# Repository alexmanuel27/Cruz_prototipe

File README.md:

# Cruz Prototype

Cruz is an autonomous optical instrument for monitoring natural waters. It is being developed in lakes for eventual use in bays. A single quartz flow cell serves a shared illumination arm with a halogen transmission source and selectable blue, red and infrared LEDs, an inline camera for transmission, and an AS7265x at 90° for fluorescence. The transmission target is 420–780 nm; fluorescence includes nominal 430 nm excitation, with additional red and infrared sources to be tested. A downstream peristaltic pump draws water through the cell. Temperature and conductivity are part of the design.

## Project files

| To work on | Open |
| --- | --- |
| Requirements and design rationale | [Functional specification](ESPECIFICACION.md) · [Decision log](DECISIONES.md) · [Optical design](docs/DISENO_OPTICO.md) |
| Mechanical assembly | [CAD guide](cad/README.md) |
| Fabrication files | [End-cap SVG for Shaper Origin](body/TAPA_SHAPER_230_PROTOTIPO.svg) · [Machining notes](body/LEEME.md) · [R3 attachment ring STL](cad/fusion_m2/ARO_AMARRE_M8_REFORZADO_R3.stl) · [R5 internal chassis STL and assembly guide for Prusa MINI](cad/fusion_m2/chasis_r5/README.md) |
| Electronics | [KiCad V8 project](electronica/cross_v8_raspberry/cross_v8_draft.kicad_pro) · [PCB status and open items](electronica/cross_v8_raspberry/LEEME_PRIMERO.md) |
| Acquisition and control | [Run the monitor](software/README.md) · [Bench tests and V8 interfaces](docs/SOFTWARE_ADQUISICION.md) |
| Test records and simulation data | [Test log](docs/REGISTRO_ENSAYOS.md) · [R3 load and ballast study](cad/fusion_m2/simulacion_amarre_2026-11-20/) · [Calibration procedures](docs/VALIDACION_Y_CALIBRACION.md) |
| Procurement records | [Purchase list](compras/LISTA_COMPRA.md) · [Technician's workbook](compras/Cruz_Shopping_List_EN_2026-10-30.xlsx) |
| Earlier designs and assembly video | [Archive guide](archivo/README.md) |

## Prototype status

The enclosure uses a horizontal clear acrylic tube with a 180 mm outer diameter, a 172 mm inner diameter and a length of 380 mm. Both Ø230 mm end caps use 10 mm acrylic. The auxiliary USB camera looks forward through the front cap. The rear cap service holes will be drilled to suit the actual fittings.

The removable R5 chassis uses two flat-printed end frames and a bolted centre bridge. The optical cradle, cover and PCB tray are removable. All six parts fit the Original Prusa MINI. Fusion v13 documents the R3 attachment ring and ballast simulation. Physical load and leak tests are pending. KiCad V8 is the editable electronics draft. The PCB is currently unrouted: all tracks, copper zones and wire jumpers were removed at Alex’s request. The schematic retains the original connections and numbered functional blocks. Single-sided CNC routing and electrical/mechanical validation remain pending. Purchase prices and quantities in the workbook are dated 30 October 2026.

The [engineering index](docs/INDICE_PROYECTO.md) links to the detailed design, build and validation records.

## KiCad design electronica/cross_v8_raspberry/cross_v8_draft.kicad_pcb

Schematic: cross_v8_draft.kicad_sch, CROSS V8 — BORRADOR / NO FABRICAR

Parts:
C1: 100uF 50V; CNC_Capacitor_THT_CP_Radial_D8_0mm_P3_50mm
C2, C3, C6, C22: 100nF; C_0805_2012Metric
C4, C5: 2u2 X7R 16V; C_0805_2012Metric
C8, C9: 1uF X7R 10V; C_0805_2012Metric
C11, C12: 100nF X7R 25V; C_0805_2012Metric
C15, C20: 22uF X7R 16V; C_1206_3216Metric
C16, C18, C19: 100nF X7R 16V; C_0805_2012Metric
C21: 4u7 X7R 50V; C_1206_3216Metric
D2: 1N4007_PILOT_REVERSE; D_DO-41_SOD81_P10.16mm_Horizontal
D7: PILOT_SIGNAL; D_DO-41_SOD81_P10.16mm_Horizontal
F1: F1_LOAD_RATING_TBD; Fuseholder_Clip-5x20mm_Littelfuse_111_Inline_P20.00x5.00mm_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
J1: RASPBERRY_PI_5_GPIO_3V3; CNC_Connector_IDC_IDC-Header_2x20_P2_54mm_Vertical
J2: MOTOR_COILS_VERIFY; CNC_Connector_PinHeader_2_54mm_PinHeader_1x04_P2_54mm_Verti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
J3: HALOGEN_12V_10W_INRUSH_TBD; TerminalBlock_Phoenix_MKDS-1,5-2-5.08_1x02_P5.08mm_Horizont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
J4: BLUE_LED_420_430nm; TerminalBlock_Phoenix_MKDS-1,5-2-5.08_1x02_P5.08mm_Horizont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
J5: ORANGE_LED_620nm; TerminalBlock_Phoenix_MKDS-1,5-2-5.08_1x02_P5.08mm_Horizont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
J6: ADS1115_INTERFACE_VERIFY; CNC_Connector_PinHeader_2_54mm_PinHeader_1x04_P2_54mm_Verti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
J7: ADS1115_A0_VERIFY; CNC_Connector_PinHeader_2_54mm_PinHeader_1x02_P2_54mm_Verti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
J8: I2C_AS7265X; CNC_Connector_PinHeader_2_54mm_PinHeader_1x04_P2_54mm_Verti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
J10: DS18B20; CNC_Connector_PinHeader_2_54mm_PinHeader_1x03_P2_54mm_Verti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
J11: SYS_SW_DESDE_INTERRUPTOR; TerminalBlock_Phoenix_MKDS-1,5-2-5.08_1x02_P5.08mm_Horizont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
J13: SYS_IN_GESTOR_EXTERNO; TerminalBlock_Phoenix_MKDS-1,5-2-5.08_1x02_P5.08mm_Horizont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
J14: TO_SWITCH_INPUT_FUSED; TerminalBlock_Phoenix_MKDS-1,5-2-5.08_1x02_P5.08mm_Horizont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
J18: EN3_8PIN_ASSIGNMENT_VERIFY; CNC_Connector_PinHeader_2_54mm_PinHeader_1x08_P2_54mm_Verti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
J19: RS485_DFR0845_UART_ADAPTER; CNC_Connector_PinHeader_2_54mm_PinHeader_1x04_P2_54mm_Verti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
J20: RS485_DFR0845_BUS_ADAPTER; CNC_Connector_PinHeader_2_54mm_PinHeader_1x04_P2_54mm_Verti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
J23: PI_5V_USBC_LEAD_VERIFY; TerminalBlock_Phoenix_MKDS-1,5-2-5.08_1x02_P5.08mm_Horizont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
J24: DS3231_5V_GND_SDA_SCL_INT_SQW; CNC_Connector_PinHeader_2_54mm_PinHeader_1x05_P2_54mm_Verti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
J25: PULSADOR_MOMENTANEO_NA_5S; CNC_Connector_PinHeader_2_54mm_PinHeader_1x02_P2_54mm_Verti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
J26: POLOLU_2814_ON_GND; CNC_Connector_PinHeader_2_54mm_PinHeader_1x02_P2_54mm_Verti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
J27: IR_TSHG6410_850nm; TerminalBlock_Phoenix_MKDS-1,5-2-5.08_1x02_P5.08mm_Horizont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
J28: EC_COAX_LIVE_SHIELD_VERIFY; CNC_Connector_PinHeader_2_54mm_PinHeader_1x02_P2_54mm_Verti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
J29: UPDI_5V_SIGNAL_GND; PinHeader_1x03_P2.54mm_Vertical
Q1, Q7, Q8, Q9: IRLZ44N; TO-220-3_Vertical
Q3, Q4: BSS138; SOT-23
R1, R2, R3, R14, R15, R16, R17, R21, R22, R24: 10k; R_0805_2012Metric
R4, R42, R44, R45: 26R 1% 0.25W; CNC_Resistor_THT_R_Axial_DIN0207_L6_3mm_D2_5mm_P7_62mm_Hori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
R5, R36, R38, R40: 470R; R_0805_2012Metric
R6, R37, R39, R41: 120k; R_0805_2012Metric
R8: 100k 1%; R_0805_2012Metric
R9: 10k 1%; R_0805_2012Metric
R10: 4k7; R_0805_2012Metric
R13: 680R; R_0805_2012Metric
R20, R23: 100k; R_0805_2012Metric
R26, R27: 4k7 DNP_VERIFY_MODULE_PULLUPS; R_0805_2012Metric; not fitted
R43, R46: 52R 1% 0.25W; CNC_Resistor_THT_R_Axial_DIN0207_L6_3mm_D2_5mm_P7_62mm_Hori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
R47: 220R 1W CURRENT_TBD; R_Axial_DIN0411_L9.9mm_D3.6mm_P15.24mm_Horizontal
U1: A4988_CARRIER_VERIFY_PINOUT; CNC_Module_Pololu_Breakout-16_15_2x20_3mm
U2: LM317_BLUE_THERMAL_TBD; TO-220-3_Vertical
U3: LTV-817; CNC_Package_DIP_DIP-4_W7_62mm
U4: R-78HE5.0-0.3_AON; CNC_Cross_R78HE5V
U5: EXTERNAL_24V_TO_5V_PI; TerminalBlock_Phoenix_MKDS-1,5-4-5.08_1x04_P5.08mm_Horizont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
U6: EXTERNAL_24V_TO_12V_OPT; TerminalBlock_Phoenix_MKDS-1,5-4-5.08_1x04_P5.08mm_Horizont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
U12: ATLAS_EC_OEM_K0.1_0x64; Atlas_EC_OEM_10pad
U14: LM317_ORANGE_THERMAL_TBD; TO-220-3_Vertical
U16: 74AHCT1G125; SOT-23-5
U17: ATtiny1604-SS; SOIC-14_3.9x8.7mm_P1.27mm

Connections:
3V3_PI: C2.1, C9.1, C18.1, C19.1, J1.1, J6.1, J8.1, J10.1, J19.4, Q3.1 (G), Q4.1 (G), R1.2, R10.2, R14.1, R22.2, R26.1, R27.1, U1.5, U1.6, U1.10, U12.3 (VCC)
5V_AON: C4.1, C5.1, C6.1, C20.1, C22.1, J24.1, J29.1, R13.1, R15.2, R16.2, R17.2, R21.2, R24.2, U4.3 (5V_OUT), U16.5 (VCC), U17.1 (VCC)
5V_PI: C8.1, C15.1, C16.1, J23.1, U5.3
12V_OPT: C11.1, C12.1, J3.1, R47.1, U2.3 (VI), U6.3, U14.3 (VI)
/BAT_SENSE: C3.1, J7.1, R8.2, R9.1
/BLUE_EN: J1.16, R36.1
/BUTTON_N: J25.1, R21.1, U17.11 (PA1)
/CUT_ACK_5V: U16.4, U17.3 (PA5)
/HAL_EN: J1.15, R5.1
/IR_EN: J1.38, R40.1
/M_DIR: J1.12, R3.1, U1.8
/M_ENABLE_N: J1.13, R1.1, U1.1
/M_STEP: J1.11, R2.1, U1.7
/ORANGE_EN: J1.36, R38.1
/PILOT_ACTIVE_N: D7.1 (K), R24.1, U3.4
/PILOT_LED_A: D2.1 (K), R13.2, U3.1
/PILOT_LOOP: D2.2 (A), J18.8, U3.2
/PILOT_SENSE: D7.2 (A), J1.22, R14.2
/POWER_OFF_ACK: J1.37, R23.1, U16.2
/POWER_ON: J26.1, R20.1, U17.13 (PA3)
/RS485_A: J18.5, J20.3
/RS485_B: J18.6, J20.4
/RS485_REF: J18.7, J20.2
/RTC_SCL: J24.4, Q4.3 (D), R16.1
/RTC_SDA: J24.3, Q3.3 (D), R15.1
/SCL: J1.5, J6.4, J8.4, Q4.2 (S), R27.2, U12.8 (SCL)
/SDA: J1.3, J6.3, J8.3, Q3.2 (S), R26.2, U12.1 (SDA)
/SHUTDOWN_REQ_N: J1.29, R22.1, U17.2 (PA4)
/SYS_FUSED: C21.1, F1.2, J14.1, U4.1 (VIN)
/SYS_IN: F1.1, J13.1
/SYS_SW: C1.1, J11.1, R8.1, U1.16, U5.1, U6.1
/TEMP_1WIRE: J1.7, J10.3, R10.1
/UPDI: J29.2, U17.10 (~RESET/PA0)
/WAKE_N: J24.5, R17.1, U17.12 (PA2)
GND: C1.2, C2.2, C3.2, C4.2, C5.2, C6.2, C8.2, C9.2, C11.2, C12.2, C15.2, C16.2, C18.2, C19.2, C20.2, C21.2, C22.2, J1.6, J1.9, J1.14, J1.20, J1.25, J1.30, J1.34, J1.39, J6.2, J7.2, J8.2, J10.2, J11.2, J13.2, J14.2, J18.4, J19.3, J23.2, J24.2, J25.2, J26.2, J29.3, Q1.3 (S), Q7.3 (S), Q8.3 (S), Q9.3 (S), R2.2, R3.2, R6.2, R9.2, R20.2, R23.2, R37.2, R39.2, R41.2, U1.2, U1.3, U1.4, U1.9, U1.15, U3.3, U4.2 (GND), U5.2, U5.4, U6.2, U6.4, U12.6 (GND), U16.1, U16.3 (GND), U17.14 (GND)
unnamed: J1.8, J19.2
unnamed: J1.10, J19.1
unnamed: J2.1, U1.12
unnamed: J2.2, U1.11
unnamed: J2.3, U1.13
unnamed: J2.4, U1.14
unnamed: J3.2, Q1.2 (D)
unnamed: J4.1, R4.2, R42.2, R43.2, U2.1 (ADJ)
unnamed: J4.2, Q7.2 (D)
unnamed: J5.1, R44.2, R45.2, R46.2, U14.1 (ADJ)
unnamed: J5.2, Q8.2 (D)
unnamed: J27.1, R47.2
unnamed: J27.2, Q9.2 (D)
unnamed: J28.1, U12.4 (PRB)
unnamed: J28.2, U12.5 (PRBG)
unnamed: Q1.1 (G), R5.2, R6.1
unnamed: Q7.1 (G), R36.2, R37.1
unnamed: Q8.1 (G), R38.2, R39.1
unnamed: Q9.1 (G), R40.2, R41.1
unnamed: R4.1, R42.1, R43.1, U2.2 (VO)
unnamed: R44.1, R45.1, R46.1, U14.2 (VO)

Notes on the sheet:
NARANJA 620nm
12V_OPT: arranque, fusibles y termica pendientes. Retornos de potencia separados del sensor.
HALOGENA 12V 10W
Pi 5: IDC40 1:1, verificar pin 1. Alimentacion USB-C; J1.2 y J1.4 sin conectar.
J13: salida SYS del gestor externo. Cargador y bateria van al gestor. F1 por dimensionar.
AZUL
08 POTENCIA OPTICA - 12V
IR 850nm
DS3231: conectar INT/SQW a J24.5 (WAKE_N). Verificar orden fisico del modulo.
01 ENTRADA Y PROTECCION
02 CONVERSION DE ALIMENTACION
03 MOTOR PERISTALTICO
04 RASPBERRY Y COMUNICACIONES
05 SENSORES Y CONDUCTIVIDAD
06 RELOJ, ARRANQUE Y APAGADO
07 DETECCION DE PILOTO
DS3231 y adaptacion I2C
Pulsador de 5 s y supervisor permanente
EC-OEM 0x64 y sonda K0.1
PRB/PRBG solo a sonda. Bus I2C de 3V3, 100 kHz.

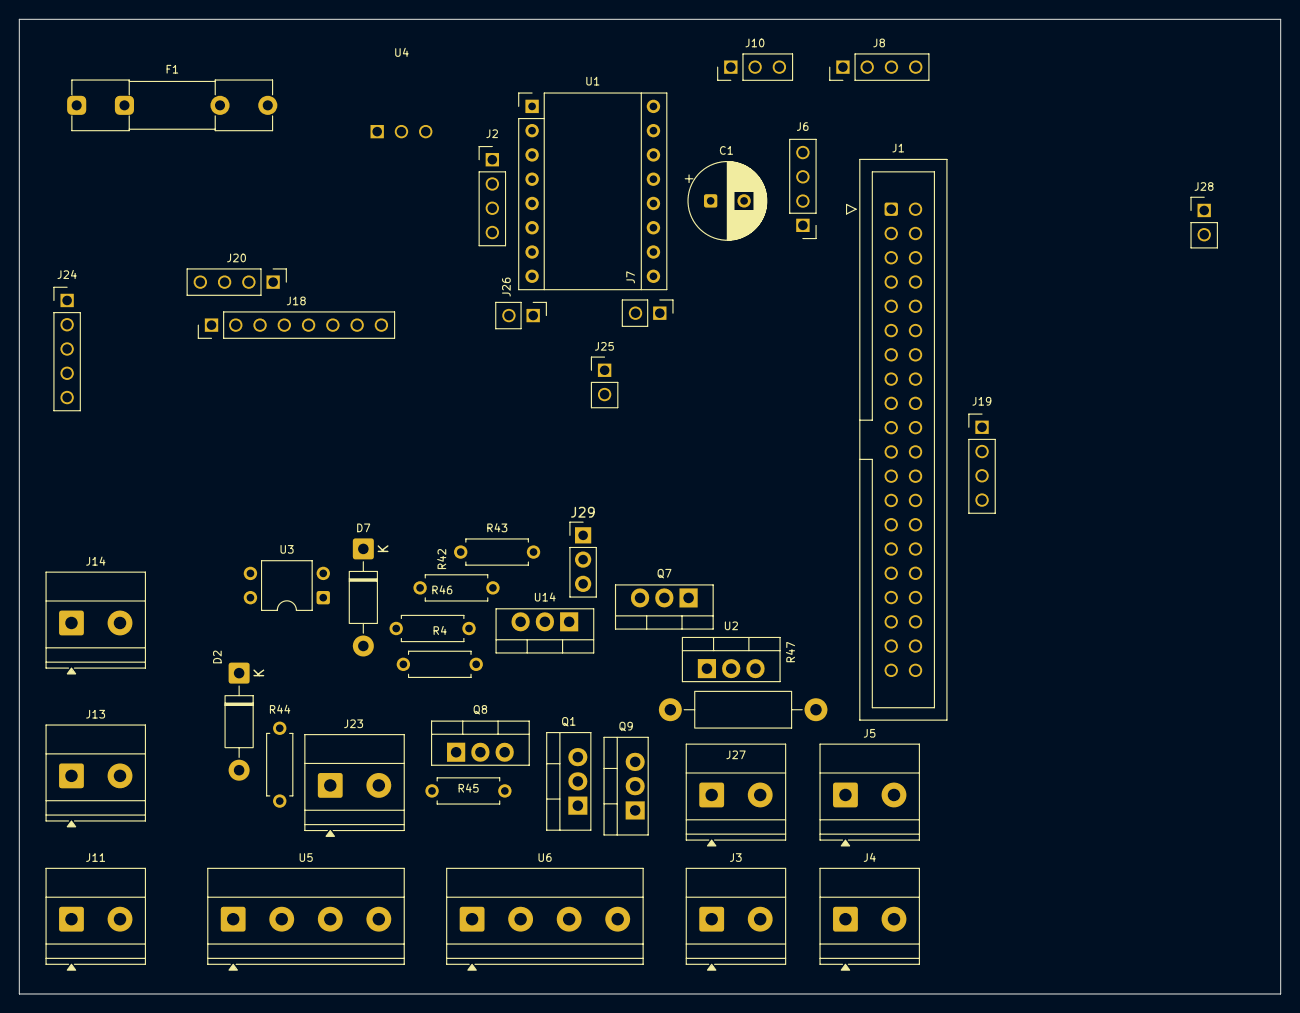
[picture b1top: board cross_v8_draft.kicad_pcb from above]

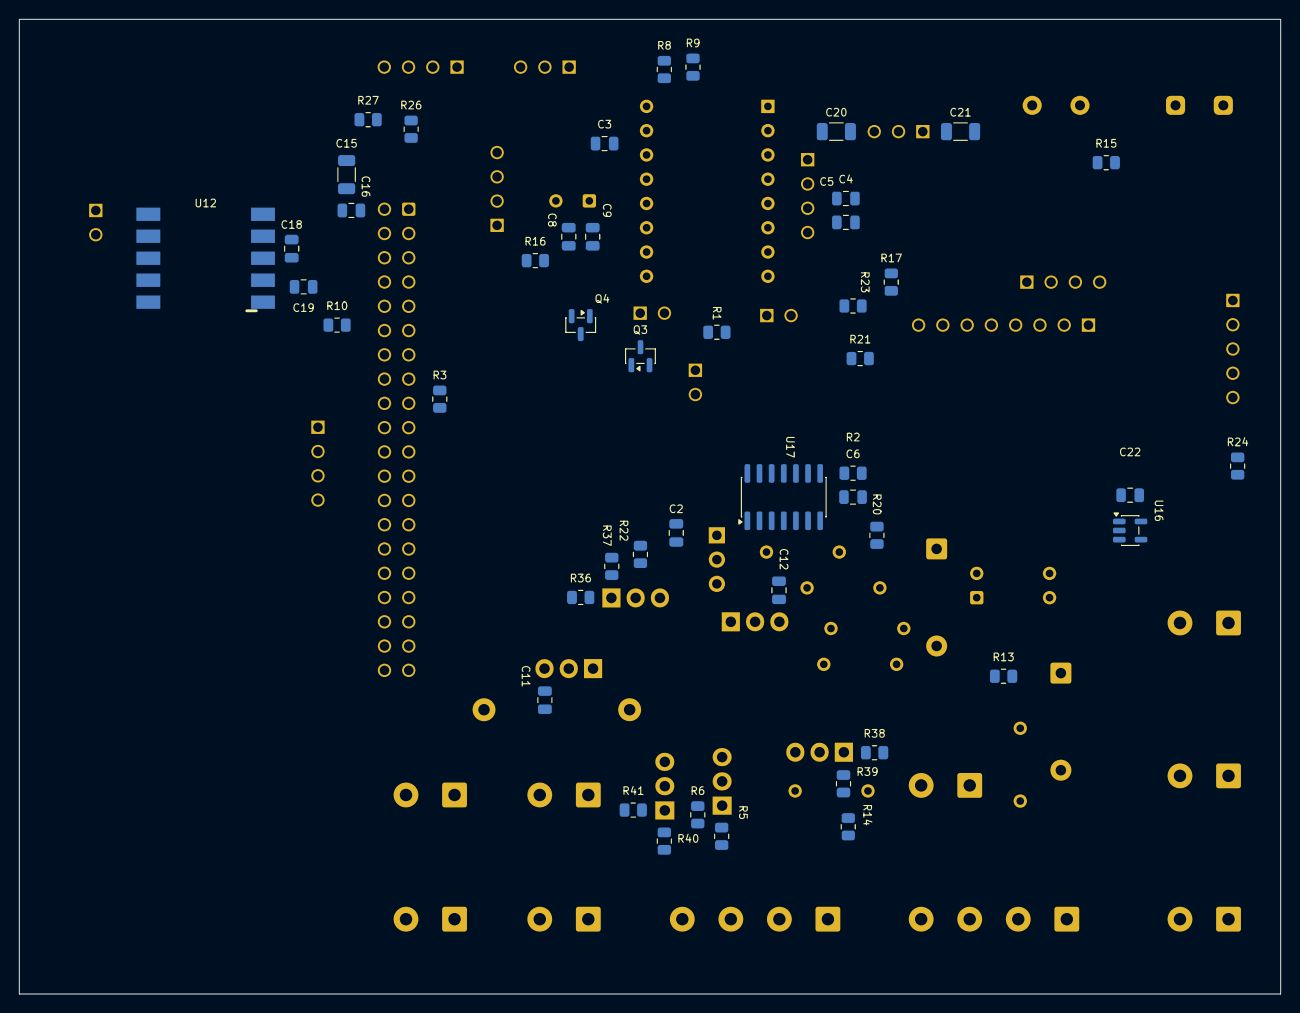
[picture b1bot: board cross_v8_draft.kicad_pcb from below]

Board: 2 copper layers, 132.0 x 102.0 mm, 91 parts (47 on the bottom side), 56 nets, no tracks yet.

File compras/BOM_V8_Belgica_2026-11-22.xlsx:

Cruz V8 · BOM para una PCB
22 nov 2026 · 91 posiciones en KiCad · 89 previstas para montar · 2 DNP · Canti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
Ref. placa | Montar | Componente | Formato | MPN fabricante | Proveedor y código | Pedido | Notas de compra y montaje | Valor en KiCad
C1 | 1 | 100 µF, 50 V, Panasonic FR | Radial Ø8 mm · paso 3,5 mm | EEU-FR1H101 | Mouser BE · 667-EEU-FR1H101 | Pedir | Polarizado. Desacoplo de la alimentación del A4988. | 100uF 50V
C2, C3, C6, C11, C12, C16, C18, C19, C22 | 9 | 100 nF, 50 V, X7R | 0805 | C0805C104K5RACTU | Mouser BE · ficha | Pedir | Una referencia de 50 V cubre los nueve condensadores de 100 nF. | 100nF · 100nF X7R 25V · 100nF X7R 16V
C4, C5 | 2 | 2,2 µF, 25 V, X7R | 0805 | C2012X7R1E225K125AB | Farnell BE · 2526260 | Pedir | El esquema especifica 16 V como mínimo. | 2u2 X7R 16V
C8, C9 | 2 | 1 µF, 25 V, X7R | 0805 | C0805C105K3RACTU | Mouser BE · ficha | Pedir | El esquema especifica 10 V como mínimo. | 1uF X7R 10V
C15, C20 | 2 | 22 µF, 16 V, X7R | 1206 | 1206YC226MAT2A | Mouser BE · 581-1206YC226MAT2A | Pedir | Carriles de 5 V. Confirmar disponibilidad en el formato de cinta cortada. | 22uF X7R 16V
C21 | 1 | 4,7 µF, 50 V, X7R | 1206 | C1206X475K5RACAUTO | Mouser BE · ficha | Pedir | En la entrada SYS_FUSED. | 4u7 X7R 50V
D2 | 1 | Diodo rectificador del piloto | DO-41 axial · paso 10,16 mm | 1N4007-E3/73 | Farnell BE · 2395843 | Pedir | Protección inversa del piloto. | 1N4007_PILOT_REVERSE
D7 | 1 | Diodo de señal del piloto | DO-41 axial · paso 10,16 mm | 1N5819-E3/54 | Farnell BE · 1336533 | Validar | Candidato Schottky de baja caída. Medir nivel bajo en GPIO 22 con el piloto act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 | PILOT_SIGNAL
F1 | 1 | Posición de fusible de carga | Clips 5×20 mm en PCB | Calibre pendiente |  | Validar | Medir corriente y pico de arranque. Alternativa de portafusible externo en la s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 | F1_LOAD_RATING_TBD
J1 | 1 | Cabezal macho IDC, 2×20 con guía | THT vertical · paso 2,54 mm | N2540-6002RB | Farnell BE · 9838309 | Pedir | Usar la cinta 1:1. Comprobar pin 1 en ambos extremos. | RASPBERRY_PI_5_GPIO_3V3
J2, J6, J8, J19, J20 | 5 | Cabezal macho 1×4 | THT vertical · paso 2,54 mm | TSW-104-07-G-S | Mouser BE · ficha | Pedir | Motor, ADS1115, AS7265x y ambos lados del adaptador RS485. | MOTOR_COILS_VERIFY · ADS1115_INTERFACE_VERIFY · I2C_AS7265X · RS485_DFR0845_UAR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
J7, J25, J26, J28 | 4 | Cabezal macho 1×2 | THT vertical · paso 2,54 mm | TSW-102-07-G-S | Mouser BE · ficha | Pedir | Entrada analógica, pulsador, mando Pololu y sonda EC. | ADS1115_A0_VERIFY · PULSADOR_MOMENTANEO_NA_5S · POLOLU_2814_ON_GND · EC_COAX_LI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
J10, J29 | 2 | Cabezal macho 1×3 | THT vertical · paso 2,54 mm | TSW-103-07-G-S | Mouser BE · ficha | Pedir | DS18B20 y programación UPDI. | DS18B20 · UPDI_5V_SIGNAL_GND
J24 | 1 | Cabezal macho 1×5 | THT vertical · paso 2,54 mm | TSW-105-07-G-S | Mouser BE · ficha | Pedir | DS3231 con INT/SQW. Cotejar el orden de los hilos. | DS3231_5V_GND_SDA_SCL_INT_SQW
J18 | 1 | Cabezal macho 1×8 | THT vertical · paso 2,54 mm | TSW-108-07-G-S | Mouser BE · ficha | Pedir | Conexión interna al EN3 de panel. | EN3_8PIN_ASSIGNMENT_VERIFY
J3, J4, J5, J11, J13, J14, J23, J27 | 8 | Bornera Phoenix Contact MKDS 1,5/2-5,08 | 2 polos · paso 5,08 mm | 1715721 | RS BE · 1930564 | Pedir | Entrada, rama conmutada, alimentación Pi y cuatro fuentes ópticas. | HALOGEN_12V_10W_INRUSH_TBD · BLUE_LED_420_430nm · ORANGE_LED_620nm · SYS_SW_DES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
U5, U6 | 2 | Bornera Phoenix Contact MKDS 1,5/4-5,08 | 4 polos · paso 5,08 mm | 1715747 | RS BE · 6487857 | Pedir | Son las dos borneras de entrada/salida de los DC/DC externos. | EXTERNAL_24V_TO_5V_PI · EXTERNAL_24V_TO_12V_OPT
Q1, Q7, Q8, Q9 | 4 | MOSFET Infineon IRLZ44N | TO-220AB vertical | IRLZ44NPBF | Farnell BE · 8651418 | Revisar inventario | Has probado esta familia con 3,3 V. Medir calentamiento y arranque en frío de l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 | IRLZ44N
Q3, Q4 | 2 | MOSFET BSS138 onsemi | SOT-23 | BSS138LT1G | Mouser BE · 863-BSS138LT1G | Pedir | Adaptación de niveles del I²C del RTC. | BSS138
R1, R2, R3, R9, R14, R15, R16, R17, R21, R22, R24 | 11 | 10 kΩ, 1 %, 0,125 W | 0805 | RC0805FR-0710KL | Mouser BE · 603-RC0805FR-0710KL | Pedir |  | 10k · 10k 1%
R5, R36, R38, R40 | 4 | 470 Ω, 1 %, 0,125 W | 0805 | RC0805FR-07470RL | Mouser BE · ficha | Pedir | Resistencias de puerta de los cuatro IRLZ44N. | 470R
R6, R37, R39, R41 | 4 | 120 kΩ, 1 %, 0,125 W | 0805 | RC0805FR-07120KL | Mouser BE · ficha | Pedir |  | 120k
R8, R20, R23 | 3 | 100 kΩ, 1 %, 0,125 W | 0805 | RC0805FR-07100KL | Mouser BE · ficha | Pedir | R8 forma el divisor de telemetría con R9. | 100k 1% · 100k
R10 | 1 | 4,7 kΩ, 1 %, 0,125 W | 0805 | RC0805FR-074K7L | Mouser BE · ficha | Pedir | Pull-up del DS18B20. | 4k7
R13 | 1 | 680 Ω, 1 %, 0,125 W | 0805 | RC0805FR-07680RL | Mouser BE · ficha | Pedir |  | 680R
R4, R42, R44, R45 | 4 | 26 Ω en KiCad · 26,1 Ω propuesto | DIN0207 axial · paso 7,62 mm | MFR-25FBF52-26R1 | Mouser BE · ficha | Validar | 1 %, 0,25 W. Si tienes las de 26 Ω que probaste, úsalas. Validar corriente con 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 | 26R 1% 0.25W
R43, R46 | 2 | 52 Ω en KiCad · 52,3 Ω propuesto | DIN0207 axial · paso 7,62 mm | MFR-25FBF52-52R3 | Mouser BE · ficha | Validar | 1 %, 0,25 W. Con 26,1 Ω ∥ 26,1 Ω ∥ 52,3 Ω, consigna ideal ≈119,7 mA. | 52R 1% 0.25W
R47 | 1 | 220 Ω, 5 %, 1 W | Axial · paso de placa 15,24 mm | PR01000102200JA100 | Farnell BE · 2614507 | Pedir | Cuerpo menor que DIN0411. Formar patas al paso de la placa. Verificar corriente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 | 220R 1W CURRENT_TBD
U1 | 1 | Portador A4988 para el motor | Módulo 2×8 · paso 2,54 mm | A4988 existente | Ficha del fabricante | Ya tienes | Ficha del Pololu como referencia. Cotejar pinout, resistencia de sense y límite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 | A4988_CARRIER_VERIFY_PINOUT
U2, U14 | 2 | Regulador ajustable LM317T ST | TO-220 vertical | LM317T | Farnell BE · 9756027 | Pedir 1 si el tuyo encaja | Se montan dos. Tienes uno. Verificar potencia disipada con los LED reales. | LM317_BLUE_THERMAL_TBD · LM317_ORANGE_THERMAL_TBD
U3 | 1 | Optoacoplador Lite-On LTV-817 | DIP-4 · ancho de filas 7,62 mm | LTV-817 | Mouser BE · ficha | Pedir | Lectura del piloto. | LTV-817
U4 | 1 | RECOM 5 V / 300 mA de espera | SIP-3 | R-78HE5.0-0.3 | Farnell BE · 3264795 | Pedir | Alimenta supervisor y RTC. Entrada 6,5–72 V según RECOM. | R-78HE5.0-0.3_AON
U12 | 1 | Módulo de conductividad Atlas EC-OEM | Módulo de 10 contactos | EC-OEM existente | Ficha del fabricante | Ya tienes | Recibe 3V3 de la Pi y comparte I²C. Verificar encaje y orientación antes de sol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 | ATLAS_EC_OEM_K0.1_0x64
U16 | 1 | Buffer lógico TI de confirmación de apagado | SOT-23-5 (DBV) | SN74AHCT1G125DBVR | Mouser BE · 595-SNAHCT1G125DBVR | Pedir | Función de apagado. Adaptación de 3,3 a 5 V. | 74AHCT1G125
U17 | 1 | Microcontrolador Microchip ATtiny1604 | SOIC-14 · paso 1,27 mm | ATTINY1604-SSNR | Mouser BE · ficha | Pedir | Programar por J29 con el firmware de pulsación de 5 s. | ATtiny1604-SS
R26, R27 | 0 | 4,7 kΩ, pull-ups opcionales | 0805 | RC0805FR-074K7L |  | DNP · sin montar | Colocar solo si la revisión del bus I²C lo requiere. Misma referencia que R10. | 4k7 DNP_VERIFY_MODULE_PULLUPS

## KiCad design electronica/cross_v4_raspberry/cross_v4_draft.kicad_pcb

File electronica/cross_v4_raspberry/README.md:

# PCB V4 — carga con batería de terminales comunes

**Estado: borrador incompleto. No fabricar, soldar ni energizar.** V4 conserva el trabajo V3 en una carpeta aparte e incorpora el ramal de carga solicitado el 2 de noviembre de 2026.

## Cambios incorporados en KiCad

- `J13`: entrada del par común del pack. La alimentación y la carga comparten el mismo positivo (`VBAT_RAW`) y el mismo negativo (`GND`).
- `F1`: fusible provisional del ramal de consumo. `J14` lleva su salida a un interruptor de potencia que aún debe diseñarse; `J11` recibe por separado la salida conmutada. **J14 y J11 no están conectados entre sí en esta placa**.
- `F2`: fusible provisional de carga, en la rama positiva entre batería y el contacto común de `K1`.
- `K1`: relé bipolar G2RL-2 de bobina 5 V; los contactos normalmente abiertos conectan `J15` a los dos bornes del pack cuando se excita. `Q2`, resistencias y diodo de rueda libre representan el control de la bobina.
- `J16`, `U3`, resistencias y diodo: circuito provisional de detección del bucle de presencia del cable. `J16` representa las dos señales de presencia, no la asignación física definitiva del conector exterior. La Raspberry lee el estado mediante GPIO25; GPIO24 controla el relé mediante Q2.
- `J17` es únicamente una entrada provisional de `5V_AON` para el relé y el piloto: **su fuente no está diseñada en esta versión**. El encendido de la Raspberry para modo servicio no está resuelto.

La apertura de K1 con la pérdida del cable depende de software y de que la Raspberry esté operativa: **no hay un enclavamiento cableado independiente ni garantía de liberación ante cuelgue**. No hay firmware de control, detector de fugas integrado, prueba de interbloqueo ni solución para cargar con batería agotada. El pinout de ocho contactos del puerto exterior, polaridad del pack, corriente del cargador, BMS, características definitivas de fusibles, conexión a la futura boya y verificación de interruptores/pistas siguen pendientes. El circuito propuesto no sustituye el cargador original ni puentea el BMS.

Las huellas de conectores/fusibles son provisionales. Se eligieron clips 5 × 20 mm y relé G2RL-2 DC5 para poder estudiar el montaje; no se ha aprobado su compra ni determinado si son adecuados para corriente, capacidad de corte DC y condiciones térmicas reales. Los pines de J15/J16 **no son el pinout del conector exterior EN3**. La placa Atlas J9 conserva una propuesta de cinco pines y necesita comprobación de revisión, orientación y soporte.

## Comprobaciones de KiCad

- Se compararon las redes exportadas por el esquema con las conexiones previstas de la placa. Durante la generación se detectó y corrigió una unión indebida de 5 V con masa, y se restauró el pin de bobina `K1.A2`. Esta comparación no valida el circuito ni la seguridad de los componentes.
- DRC con paridad: **106 conexiones sin trazar**, **25 avisos de serigrafía** y **0 diferencias de paridad**. La placa no es fabricable.
- ERC: **126 incidencias**: 2 errores de alimentación no declarada, 81 avisos de puntos fuera de la rejilla y 43 avisos de discrepancia de símbolos. Se requiere revisar y ordenar el esquema, resolver ERC y comprobar visualmente cada conexión.
- No se han calculado pistas ni verificado rutas de corriente, ventilación o temperatura. No hay pruebas físicas.

## Fusion

El STEP de referencia es [`PCB_V4_BORRADOR_NO_FABRICAR.step`](../../cad/fusion_m2/PCB_V4_BORRADOR_NO_FABRICAR.step). Se importó como `PCB_V4_CARGA_BORRADOR_NO_FABRICAR` al documento activo `Cross_M2_horizontal_design`; se ocultó la referencia V3 sin borrarla. **El documento de Fusion quedó sin guardar.** La colocación es provisional, sin taladros de fijación ni cálculo de interferencias. Actualización 3D: se incorporaron modelos de referencia del relé y A4988, zócalos y envolventes aproximadas de disipador y fusibles. Procedencia, hipótesis y componentes aún pendientes en [modelos 3D](modelos_3d/README.md). Los componentes y conectores no están aprobados. Los DC/DC y otros módulos de potencia tampoco se han integrado.

Fuentes: [ficha Omron G2RL](https://omronfs.omron.com/en_US/ecb/products/pdf/en-g2rl.pdf), [AO3400A](https://www.aosmd.com/products/mosfets/low-voltage-mosfets-12v-30v/ao3400a), [DFR1015](https://www.dfrobot.com/product-2599.html), [Atlas carrier Gen 2](https://files.atlas-scientific.com/electrically-isolated-ezo-carrier-board.pdf).

**Actualización de Fusion:** el STEP más reciente es `PCB_V4_REFERENCIAS_3D_BORRADOR.step`; la versión anterior quedó oculta sin borrar. Se mantienen las limitaciones y solapamientos de referencias previos. La placa sigue sin rutear ni validar.

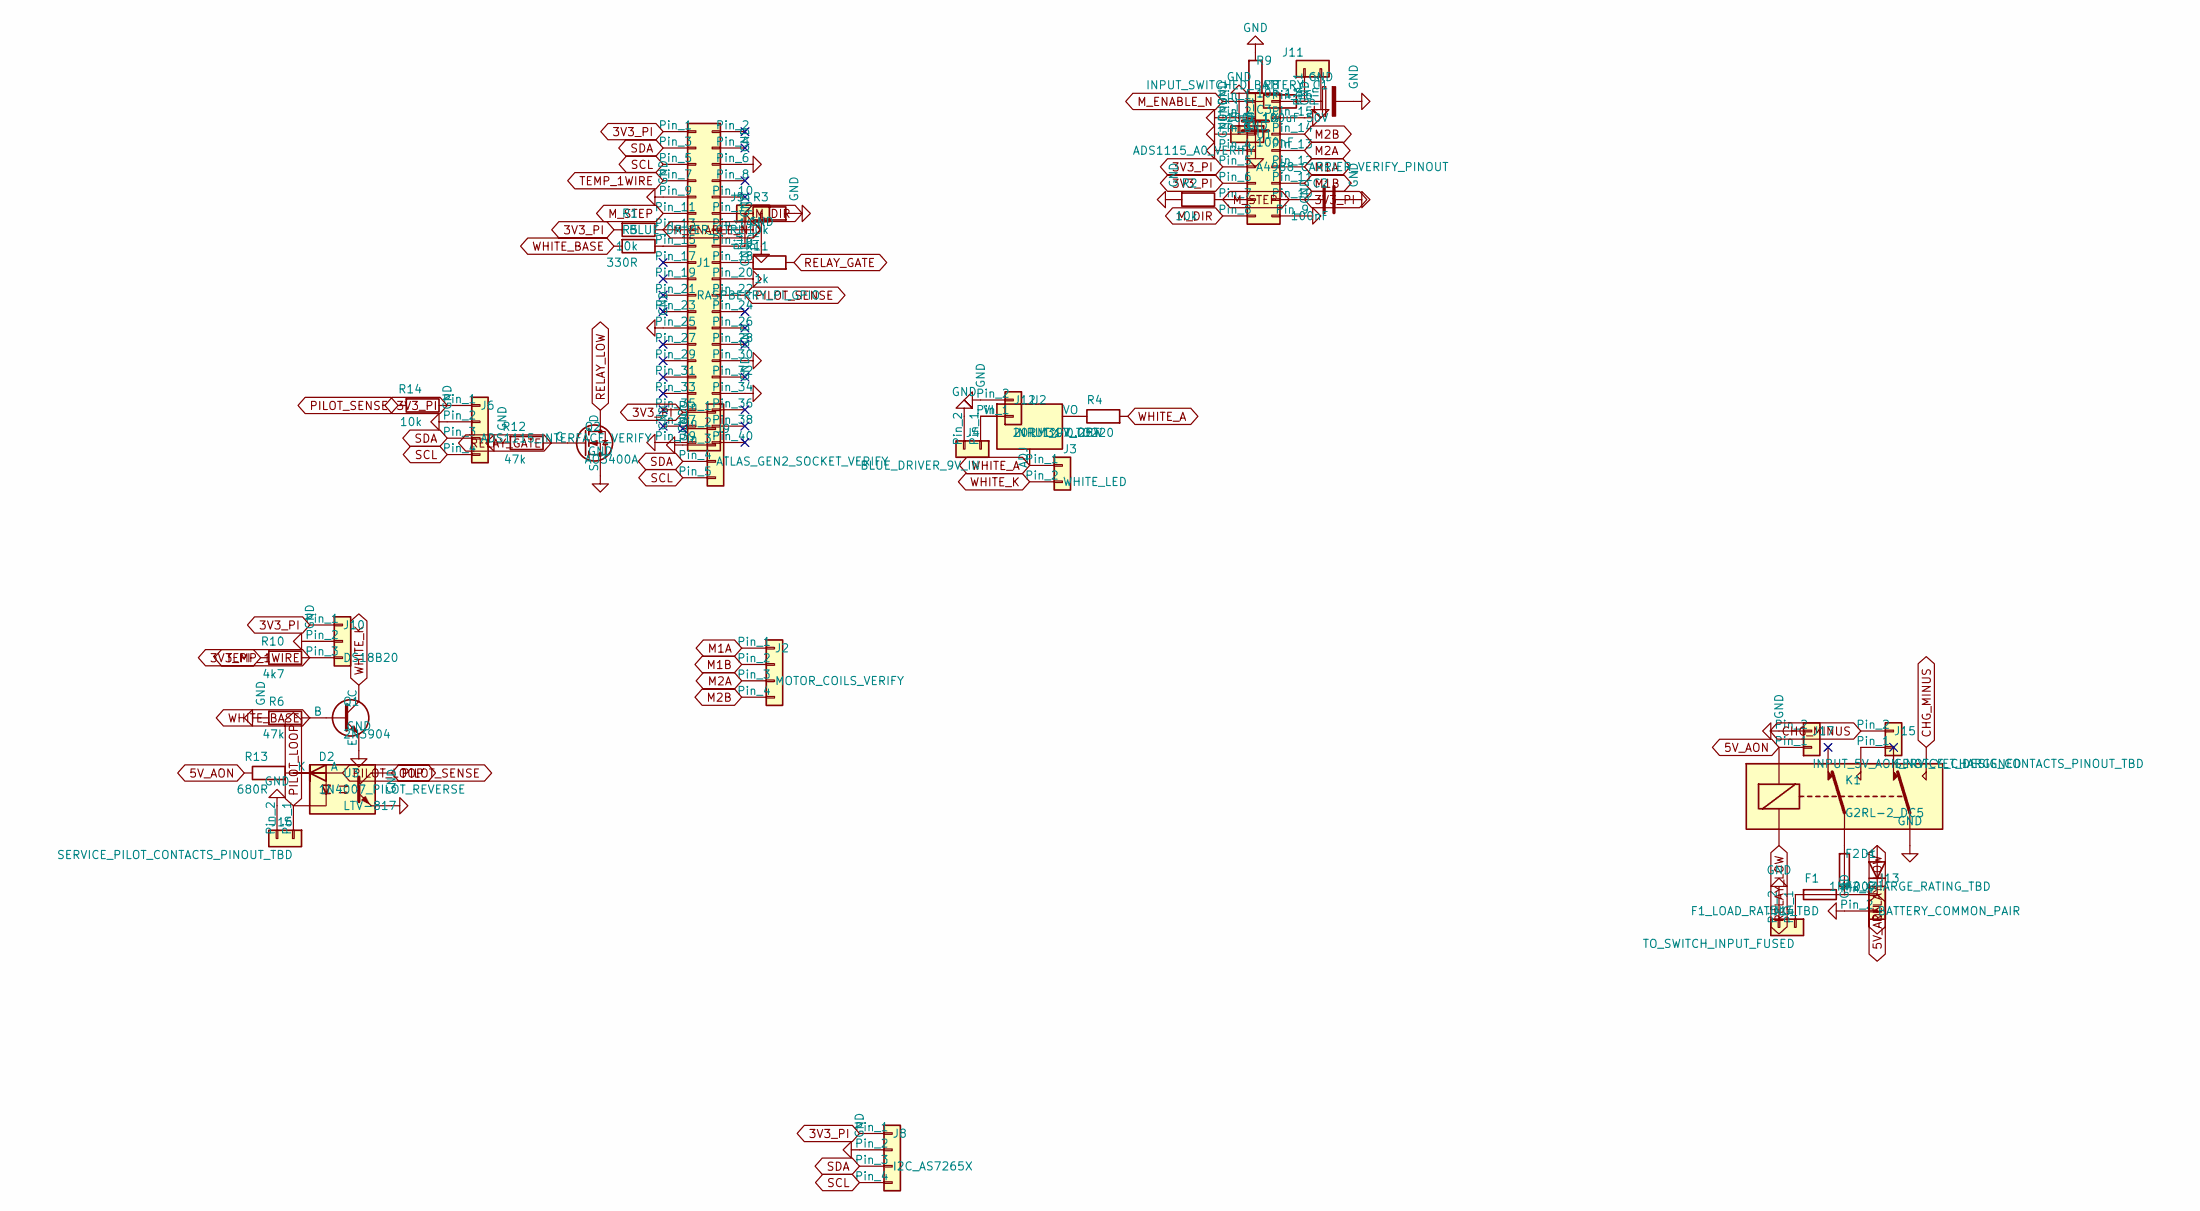
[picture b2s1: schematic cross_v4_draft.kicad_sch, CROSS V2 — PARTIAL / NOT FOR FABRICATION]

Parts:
C1: 100uF 50V; CP_Radial_D8.0mm_P3.50mm
C2, C3: 100nF; C_Disc_D5.0mm_W2.5mm_P5.00mm
D1: 1N4007; D_DO-41_SOD81_P10.16mm_Horizontal
D2: 1N4007_PILOT_REVERSE; D_DO-41_SOD81_P10.16mm_Horizontal
F1: F1_LOAD_RATING_TBD; Fuseholder_Clip-5x20mm_Littelfuse_111_Inline_P20.00x5.00mm_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
F2: F2_CHARGE_RATING_TBD; Fuseholder_Clip-5x20mm_Littelfuse_111_Inline_P20.00x5.00mm_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
J1: RASPBERRY_PI_GPIO; PinHeader_2x20_P2.54mm_Vertical
J2: MOTOR_COILS_VERIFY; PinHeader_1x04_P2.54mm_Vertical
J3: WHITE_LED; PinHeader_1x02_P2.54mm_Vertical
J4: BLUE_DRIVER_9V_IN; PinHeader_1x02_P2.54mm_Vertical
J5: BLUE_DRIVER_CTRL; PinHeader_1x02_P2.54mm_Vertical
J6: ADS1115_INTERFACE_VERIFY; PinHeader_1x04_P2.54mm_Vertical
J7: ADS1115_A0_VERIFY; PinHeader_1x02_P2.54mm_Vertical
J8: I2C_AS7265X; PinHeader_1x04_P2.54mm_Vertical
J9: ATLAS_GEN2_SOCKET_VERIFY; PinSocket_1x05_P2.54mm_Vertical
J10: DS18B20; PinHeader_1x03_P2.54mm_Vertical
J11: INPUT_SWITCHED_BATTERY; PinHeader_1x02_P2.54mm_Vertical
J12: INPUT_9V_OPT; PinHeader_1x02_P2.54mm_Vertical
J13: BATTERY_COMMON_PAIR; PinHeader_1x02_P2.54mm_Vertical
J14: TO_SWITCH_INPUT_FUSED; PinHeader_1x02_P2.54mm_Vertical
J15: SERVICE_CHARGE_CONTACTS_PINOUT_TBD; PinHeader_1x02_P2.54mm_Vertical
J16: SERVICE_PILOT_CONTACTS_PINOUT_TBD; PinHeader_1x02_P2.54mm_Vertical
J17: INPUT_5V_AON_NOT_YET_DESIGNED; PinHeader_1x02_P2.54mm_Vertical
K1: G2RL-2_DC5; Relay_DPDT_Omron_G2RL-2
Q1: 2N3904; TO-92_Inline
Q2: AO3400A; SOT-23
R1, R2, R3, R14: 10k; R_Axial_DIN0207_L6.3mm_D2.5mm_P7.62mm_Horizontal
R4: 20R 1% 0.25W; R_Axial_DIN0207_L6.3mm_D2.5mm_P7.62mm_Horizontal
R5: 330R; R_Axial_DIN0207_L6.3mm_D2.5mm_P7.62mm_Horizontal
R6, R12: 47k; R_Axial_DIN0207_L6.3mm_D2.5mm_P7.62mm_Horizontal
R8: 100k 1%; R_Axial_DIN0207_L6.3mm_D2.5mm_P7.62mm_Horizontal
R9: 10k 1%; R_Axial_DIN0207_L6.3mm_D2.5mm_P7.62mm_Horizontal
R10: 4k7; R_Axial_DIN0207_L6.3mm_D2.5mm_P7.62mm_Horizontal
R11: 1k; R_Axial_DIN0207_L6.3mm_D2.5mm_P7.62mm_Horizontal
R13: 680R; R_Axial_DIN0207_L6.3mm_D2.5mm_P7.62mm_Horizontal
U1: A4988_CARRIER_VERIFY_PINOUT; Pololu_Breakout-16_15.2x20.3mm
U2: LM317_TO220; TO-220-3_Vertical
U3: LTV-817; DIP-4_W7.62mm

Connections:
3V3_PI: C2.1, J1.1, J6.1, J8.1, J9.1, J10.1, R1.2, R10.2, R14.1, U1.5, U1.6, U1.10
5V_AON: D1.1 (K), J17.1, K1.A1, R13.1
CHG_MINUS: J15.2, K1.24
GND: C1.2, C2.2, C3.2, J1.6, J1.9, J1.14, J1.20, J1.25, J1.30, J1.34, J1.39, J4.2, J5.2, J6.2, J7.2, J8.2, J9.3, J10.2, J11.2, J12.2, J13.2, J14.2, J16.2, J17.2, K1.21, Q1.1 (E), Q2.2 (S), R2.2, R3.2, R6.2, R9.2, R12.2, U1.2, U1.3, U1.4, U1.9, U1.15, U3.3
M1A: J2.1, U1.12
M1B: J2.2, U1.11
M2A: J2.3, U1.13
M2B: J2.4, U1.14
M_DIR: J1.12, R3.1, U1.8
M_ENABLE_N: J1.13, R1.1, U1.1
M_STEP: J1.11, R2.1, U1.7
unnamed: D2.1 (K), R13.2, U3.1
unnamed: F2.2, K1.11
unnamed: J1.15, R5.1
unnamed: J1.16, J5.1
unnamed: J1.18, R11.1
unnamed: C3.1, J7.1, R8.2, R9.1
unnamed: C1.1, J11.1, R8.1, U1.16
unnamed: J4.1, J12.1, U2.3 (VI)
unnamed: F1.1, F2.1, J13.1
unnamed: F1.2, J14.1
unnamed: J15.1, K1.14
unnamed: R4.1, U2.2 (VO)
PILOT_LOOP: D2.2 (A), J16.1, U3.2
PILOT_SENSE: J1.22, R14.2, U3.4
RELAY_GATE: Q2.1 (G), R11.2, R12.1
RELAY_LOW: D1.2 (A), K1.A2, Q2.3 (D)
SCL: J1.5, J6.4, J8.4, J9.5
SDA: J1.3, J6.3, J8.3, J9.4
TEMP_1WIRE: J1.7, J10.3, R10.1
WHITE_A: J3.1, R4.2, U2.1 (ADJ)
WHITE_BASE: Q1.2 (B), R5.2, R6.1
WHITE_K: J3.2, Q1.3 (C)

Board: 2 copper layers, 43 parts (0 on the bottom side), 33 nets, no tracks yet.

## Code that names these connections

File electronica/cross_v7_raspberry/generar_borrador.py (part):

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for pin in [2,4,17,19,21,23,24,26,27,28,31,32,33,35,36,38,40]: p[pin] += NC
# Driver carrier has Pololu-compatible pin order: confirm physical red carrier before insertion.
m=part('Connector_Generic','Conn_02x08_Counter_Clockwise','U1','A4988_CARRIER_VERIFY_PINOUT','Module:Pololu_Breakout-16_15.2x20.3mm')
for pin,n in {1:'M_ENABLE_N',2:'GND',3:'GND',4:'GND',5:'3V3_PI',6:'3V3_PI',7:'M_STEP',8:'M_DIR',9:'GND',10:'3V3_PI',11:'M1B',12:'M1A',13:'M2A',14:'M2B',15:'GND',16:'VBAT_SW'}.items(): net(n,m[pin])
r('R1','10k','M_ENABLE_N','3V3_PI');r('R2','10k','M_STEP','GND');r('R3','10k','M_DIR','GND')
c=part('Device','C_Polarized','C1','100uF 50V','Capacitor_THT:CP_Radial_D8.0mm_P3.50mm');net('VBAT_SW',c[1]);net('GND',c[2])
c=part('Device','C','C2','100nF',cap);net('3V3_PI',c[1]);net('GND',c[2])
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# Common battery pair and dual isolated charging contacts; fuse ratings to be selected.
connector('J13','BATTERY_COMMON_PAIR',2,['VBAT_RAW','GND'])
connector('J14','TO_SWITCH_INPUT_FUSED',2,['VBAT_FUSED','GND'])
connector('J18','EN3_8PIN_ASSIGNMENT_VERIFY',8,['CHG_PLUS','CHG_MINUS',None,'GND','RS485_A','RS485_B','RS485_REF','PILOT_LOOP'])
connector('J19','RS485_DFR0845_UART_ADAPTER',4,['UART_RX','UART_TX','GND','3V3_PI'])
connector('J20','RS485_DFR0845_BUS_ADAPTER',4,[None,'RS485_REF','RS485_A','RS485_B'])
connector('J23','PI_5V_USBC_LEAD_VERIFY',2,['5V_PI','GND'])
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f=part('Device','Fuse','F1','F1_LOAD_RATING_TBD',fusefp);net('VBAT_RAW',f[1]);net('VBAT_FUSED',f[2])
f=part('Device','Fuse','F2','F2_CHARGE_RATING_TBD',fusefp);net('VBAT_RAW',f[1]);net('CHG_FUSED',f[2])
k=part('Relay','G2RL-2','K1','G2RL-2_DC5','Relay_THT:Relay_DPDT_Omron_G2RL-2')
for pin,n in {'A1':'5V_AON','A2':'RELAY_LOW','11':'CHG_FUSED','14':'CHG_PLUS','21':'GND','24':'CHG_MINUS'}.items():net(n,k[pin])
k['12'] += NC
k['22'] += NC
q2=part('Transistor_FET','AO3400A','Q2','AO3400A','Package_TO_SOT_SMD:SOT-23')
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net('Q5_BASE',p['B']);net('GND',p['E']);net('SET_NODE',p['C'])
r('R20','100k','POWER_ON','GND');r('R23','100k','HOLD_PI','GND')
u=part('4xxx','4013','U8','CD4013_LATCH_PROVISIONAL','Package_DIP:DIP-14_W7.62mm')
for pin,n in {5:'GND',3:'GND',6:'SET_NODE',4:'HOLD_PI',1:'POWER_ON',9:'GND',11:'GND',8:'GND',10:'GND',14:'3V3_AON',7:'GND'}.items():net(n,u[pin])
for pin in [2,12,13]:u[pin] += NC
p=part('Device','C','C6','100nF',cap);net('3V3_AON',p[1]);net('GND',p[2])
# Hardware charge interlock; independent of Pi command when pilot loop is open.
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# Blue driver is disabled during Pi boot by a pull-up and shunt FET; active-low GPIO.
r('R25','4k7','BLUE_GATE','3V3_PI')
p=part('Transistor_FET','AO3400A','Q7','BLUE_DISABLE_FET','Package_TO_SOT_SMD:SOT-23');net('BLUE_GATE',p['G']);net('BLUE_CTRL',p['D']);net('GND',p['S'])
d=part('Diode','1N5819','D8','BLUE_GPIO_INVERT','Diode_THT:D_DO-41_SOD81_P10.16mm_Horizontal');net('BLUE_GATE',d['A']);net('BLUE_EN',d['K'])
# Magnet N/O reed is read by Pi and can request wake. Separate diodes avoid powering unpowered Pi GPIO.
connector('J25','MAGNETIC_REED_NORMALLY_OPEN',2,['MAG_N','GND'])
r('R21','10k','MAG_N','3V3_AON');r('R22','10k','SW_SENSE','3V3_PI')
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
